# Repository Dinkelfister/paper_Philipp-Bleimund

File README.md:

# Facharbeit_Philipp-Bleimund
 All files used in Philipp Bleimunds paper
 
 Quick start:
 
- Download the repository.  
- The EAGLE folder is for the PCB design.  
- The FUSION folder is for 3D models of the finished PCB.  
- The runtimeCalculations folder is the programm used for my runtime calculations on the RaspberryPi (try yourself).  
- The usedGrafics folder contains all used grafics in my paper. Both in .pdf and .svg available.  
- The Sources folder contains .html and .pdf versions of the sources i used.

!disclaimer! while syncronysing Git with eclypse all my folders were deleted and i can only present decompiled code from my .jar files :(

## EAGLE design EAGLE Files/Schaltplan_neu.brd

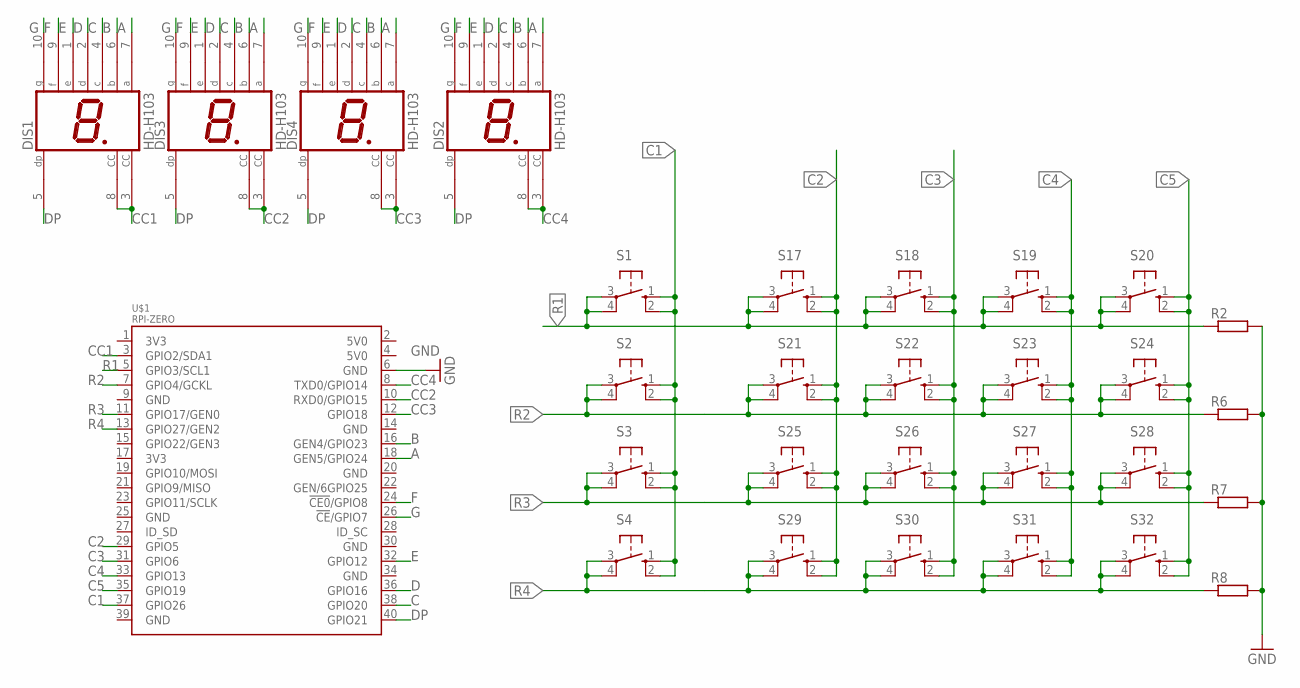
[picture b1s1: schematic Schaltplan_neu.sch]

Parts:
DIS1, DIS2, DIS3, DIS4: HD-H103; HDSP-M
R2, R6, R7, R8: R-EU_0207/10; 0207/10
S1, S2, S3, S4, S17, S18, S19, S20, S21, S22, S23, S24, S25, S26, S27, S28, S29, S30, S31, S32: 10-XX; B3F-10XX
U$1: RPI-ZERO; RASP_PI_ZERO_BOARD_FULL

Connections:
A: DIS1.7 (A), DIS2.7 (A), DIS3.7 (A), DIS4.7 (A), U$1.18 (GEN5/GPIO24)
B: DIS1.6 (B), DIS2.6 (B), DIS3.6 (B), DIS4.6 (B), U$1.16 (GEN4/GPIO23)
C: DIS1.4 (C), DIS2.4 (C), DIS3.4 (C), DIS4.4 (C), U$1.38 (GPIO20)
C1: S1.1 (S), S1.2 (S1), S2.1 (S), S2.2 (S1), S3.1 (S), S3.2 (S1), S4.1 (S), S4.2 (S1), U$1.37 (GPIO26)
C2: S17.1 (S), S17.2 (S1), S21.1 (S), S21.2 (S1), S25.1 (S), S25.2 (S1), S29.1 (S), S29.2 (S1), U$1.29 (GPIO5)
C3: S18.1 (S), S18.2 (S1), S22.1 (S), S22.2 (S1), S26.1 (S), S26.2 (S1), S30.1 (S), S30.2 (S1), U$1.31 (GPIO6)
C4: S19.1 (S), S19.2 (S1), S23.1 (S), S23.2 (S1), S27.1 (S), S27.2 (S1), S31.1 (S), S31.2 (S1), U$1.33 (GPIO13)
C5: S20.1 (S), S20.2 (S1), S24.1 (S), S24.2 (S1), S28.1 (S), S28.2 (S1), S32.1 (S), S32.2 (S1), U$1.35 (GPIO19)
CC1: DIS1.3 (CC), DIS1.8 (CC), U$1.3 (GPIO2/SDA1)
CC2: DIS3.3 (CC), DIS3.8 (CC), U$1.10 (RXD0/GPIO15)
CC3: DIS4.3 (CC), DIS4.8 (CC), U$1.12 (GPIO18)
CC4: DIS2.3 (CC), DIS2.8 (CC), U$1.8 (TXD0/GPIO14)
D: DIS1.2 (D), DIS2.2 (D), DIS3.2 (D), DIS4.2 (D), U$1.36 (GPIO16)
DP: DIS1.5 (DP), DIS2.5 (DP), DIS3.5 (DP), DIS4.5 (DP), U$1.40 (GPIO21)
E: DIS1.1 (E), DIS2.1 (E), DIS3.1 (E), DIS4.1 (E), U$1.32 (GPIO12)
F: DIS1.9 (F), DIS2.9 (F), DIS3.9 (F), DIS4.9 (F), U$1.24 (!CE0!/GPIO8)
G: DIS1.10 (G), DIS2.10 (G), DIS3.10 (G), DIS4.10 (G), U$1.26 (!CE!/GPIO7)
GND: R2.2, R6.2, R7.2, R8.2, U$1.6 (GND)
R1: R2.1, S1.3, S1.4 (P1), S17.3, S17.4 (P1), S18.3, S18.4 (P1), S19.3, S19.4 (P1), S20.3, S20.4 (P1), U$1.5 (GPIO3/SCL1)
R2: R6.1, S2.3, S2.4 (P1), S21.3, S21.4 (P1), S22.3, S22.4 (P1), S23.3, S23.4 (P1), S24.3, S24.4 (P1), U$1.7 (GPIO4/GCKL)
R3: R7.1, S3.3, S3.4 (P1), S25.3, S25.4 (P1), S26.3, S26.4 (P1), S27.3, S27.4 (P1), S28.3, S28.4 (P1), U$1.11 (GPIO17/GEN0)
R4: R8.1, S4.3, S4.4 (P1), S29.3, S29.4 (P1), S30.3, S30.4 (P1), S31.3, S31.4 (P1), S32.3, S32.4 (P1), U$1.13 (GPIO27/GEN2)

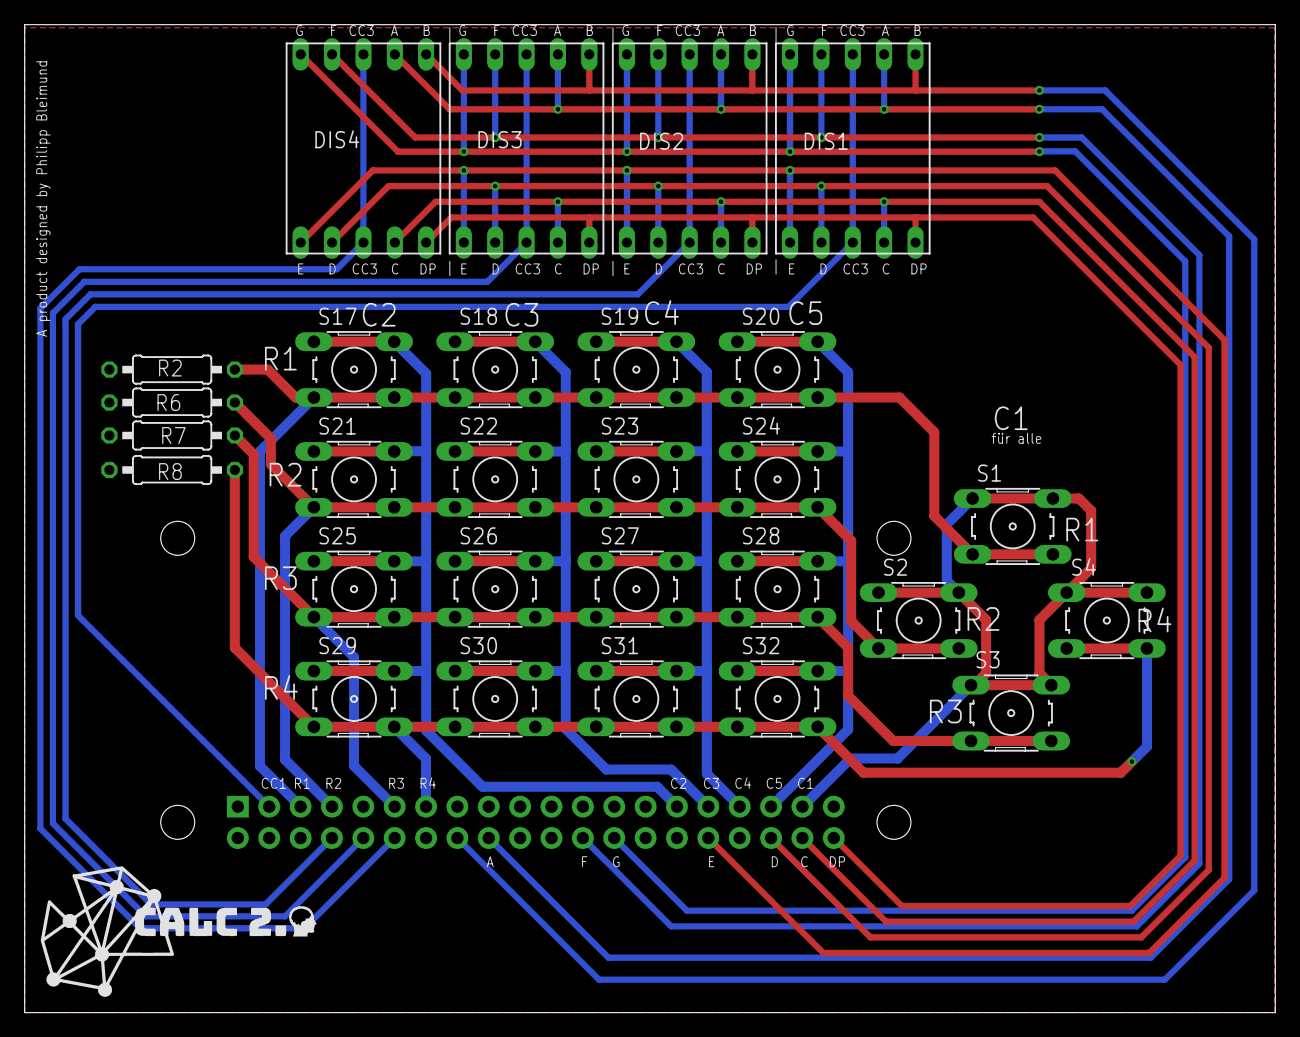
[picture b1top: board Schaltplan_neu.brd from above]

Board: 2 copper layers, 101.3 x 80.0 mm, 29 parts (1 on the bottom side), 22 nets.

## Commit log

2021-03-20 this repository is used for Philipp Bleimund´s paper
2021-03-23 Create introduction
2021-03-23 Create Video Facharbeit
